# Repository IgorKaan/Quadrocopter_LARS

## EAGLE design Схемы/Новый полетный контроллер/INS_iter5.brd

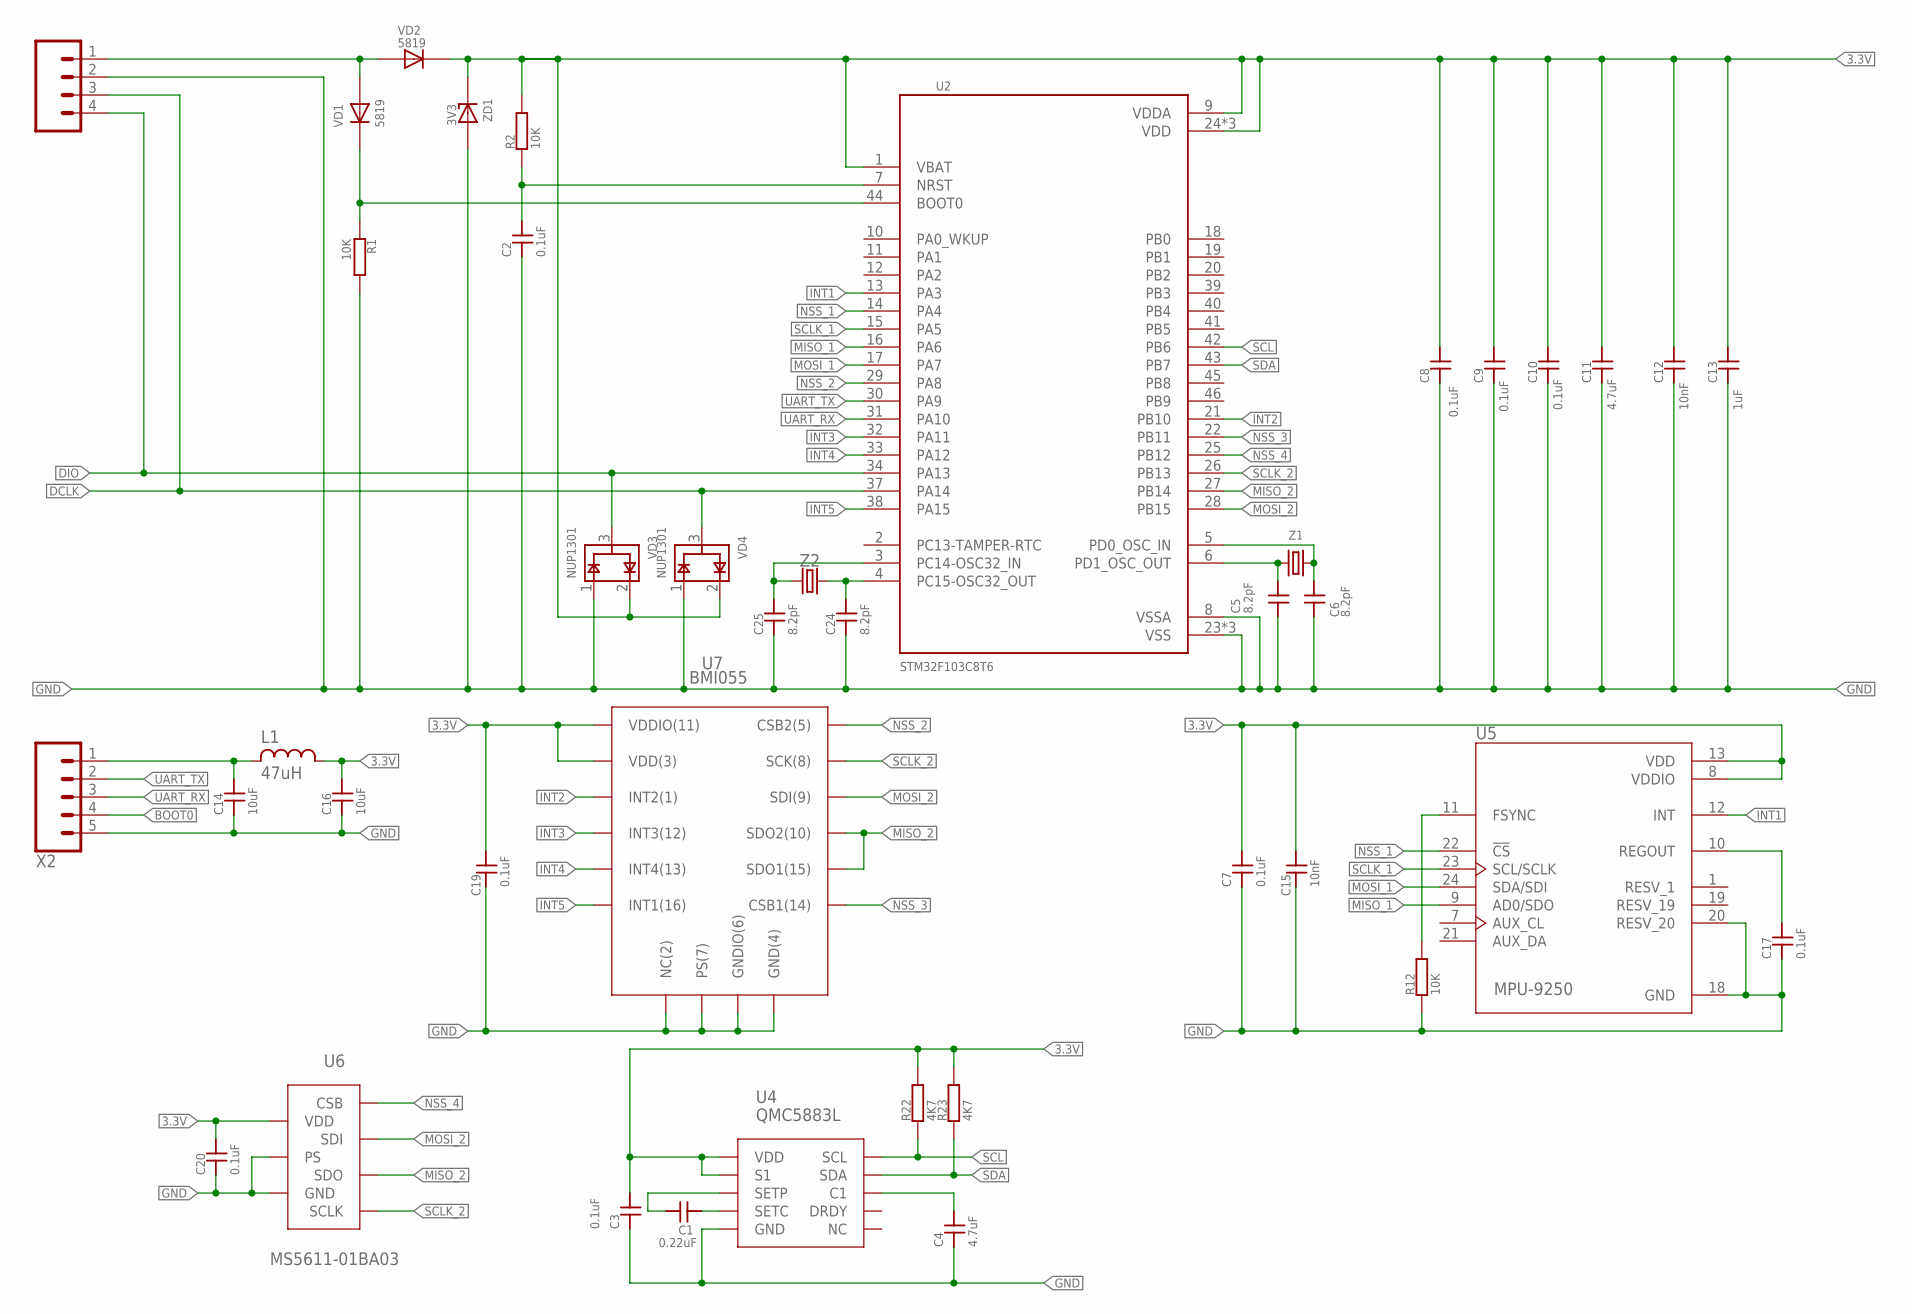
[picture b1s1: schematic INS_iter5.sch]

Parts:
C1: 0.22uF; 0402; VOLTAGE 50V
C2, C3, C7, C8, C9, C10, C17, C19, C20: 0.1uF; 0402; VOLTAGE 50V
C4, C11: 4.7uF; 0402; VOLTAGE 50V
C5, C6, C24, C25: 8.2pF; 0402; VOLTAGE 50V
C12, C15: 10nF; 0402; VOLTAGE 50V
C13: 1uF; 0402; VOLTAGE 50V
C14, C16: 10uF; 0402; VOLTAGE 6.3V
L1: 47uH; 0603_SMALL
R1, R2, R12: 10K; 0402
R22, R23: 4K7; 0402
U2: STM32F103C8T6; QFP50P900X900X160-48N
U4: QMC5883L; QFN16(3X3)NOPAD
U5: MPU-9250; QFN40P300X300X105-24N
U6: MS5611-01BA03; QFN5X3
U7: BMI055; LGA16PIN
VD1, VD2: 5819; 0402
VD3, VD4: NUP1301; SOT23
X1: 1X4DUPON; 1X04DUPON_2MM
X2: 1X5FFC5-1MM; FFC-1MM_5
Z1: 8MHz; CRYSTAL-SMD-3.2X2.5MM
Z2: CRYSTAL2FOOT; CRYSTAL-SMD-3.2X1.5X90MM
ZD1: 3V3; SOD-323

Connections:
3.3V: C3.2, C7.2, C8.2, C9.2, C10.2, C11.2, C12.2, C13.2, C15.2, C16.2, C19.2, C20.2, L1.P$2 (2), R2.2, R22.2, R23.2, U2.1 (VBAT), U2.9 (VDDA), U2.24 (VDD), U2.36 (VDD), U2.48 (VDD), U4.2 (VDD), U4.4 (S1), U4.13 (VDD), U5.8 (VDDIO), U5.13 (VDD), U6.P$4 (VDD), U7.P$3 (VDD(3)), U7.P$11 (VDDIO(11)), VD2.1 (C), VD3.2 (VCC), VD4.2 (VCC), ZD1.2 (C)
3.3V_S: VD1.2 (A), VD2.2 (A), X1.1
BOOT0: R1.1, U2.44 (BOOT0), VD1.1 (C), X2.4
DCLK: U2.37 (PA14), VD4.3 (I/O), X1.3
DIO: U2.34 (PA13), VD3.3 (I/O), X1.4
GND: C2.1, C3.1, C4.1, C5.1, C6.1, C7.1, C8.1, C9.1, C10.1, C11.1, C12.1, C13.1, C14.1, C15.1, C16.1, C17.1, C19.1, C20.1, C24.1, C25.1, R1.2, R12.1, U2.8 (VSSA), U2.23 (VSS), U2.35 (VSS), U2.47 (VSS), U4.9 (GND), U4.11 (GND), U5.18 (GND), U5.20 (RESV_20), U6.P$2 (GND), U6.P$3 (PS), U7.P$2 (NC(2)), U7.P$4 (GND(4)), U7.P$6 (GNDIO(6)), U7.P$7 (PS(7)), VD3.1 (GND), VD4.1 (GND), X1.2, X2.5, ZD1.1 (A)
INT1: U2.13 (PA3), U5.12 (INT)
INT2: U2.21 (PB10), U7.P$1 (INT2(1))
INT3: U2.32 (PA11), U7.P$12 (INT3(12))
INT4: U2.33 (PA12), U7.P$13 (INT4(13))
INT5: U2.38 (PA15), U7.P$16 (INT1(16))
MISO_1: U2.16 (PA6), U5.9 (AD0/SDO)
MISO_2: U2.27 (PB14), U6.P$7 (SDO), U7.P$10 (SDO2(10)), U7.P$15 (SDO1(15))
MOSI_1: U2.17 (PA7), U5.24 (SDA/SDI)
MOSI_2: U2.28 (PB15), U6.P$6 (SDI), U7.P$9 (SDI(9))
unnamed: C25.2, U2.3 (PC14-OSC32_IN), Z2.P$1 (1)
unnamed: C2.2, R2.1, U2.7 (NRST)
unnamed: C24.2, U2.4 (PC15-OSC32_OUT), Z2.P$2 (2)
unnamed: C17.2, U5.10 (REGOUT)
unnamed: R12.2, U5.11 (FSYNC)
unnamed: C14.2, L1.P$1 (1), X2.1
unnamed: C5.2, U2.6 (PD1_OSC_OUT), Z1.1
unnamed: C6.2, U2.5 (PD0_OSC_IN), Z1.3 (2)
unnamed: C1.2, U4.12 (SETC)
unnamed: C1.1, U4.8 (SETP)
unnamed: C4.2, U4.10 (C1)
NSS_1: U2.14 (PA4), U5.22 (!CS)
NSS_2: U2.29 (PA8), U7.P$5 (CSB2(5))
NSS_3: U2.22 (PB11), U7.P$14 (CSB1(14))
NSS_4: U2.25 (PB12), U6.P$1 (CSB), U6.P$8 (CSB)
SCL: R22.1, U2.42 (PB6), U4.1 (SCL)
SCLK_1: U2.15 (PA5), U5.23 (SCL/SCLK)
SCLK_2: U2.26 (PB13), U6.P$5 (SCLK), U7.P$8 (SCK(8))
SDA: R23.1, U2.43 (PB7), U4.16 (SDA)
UART_RX: U2.31 (PA10), X2.3
UART_TX: U2.30 (PA9), X2.2

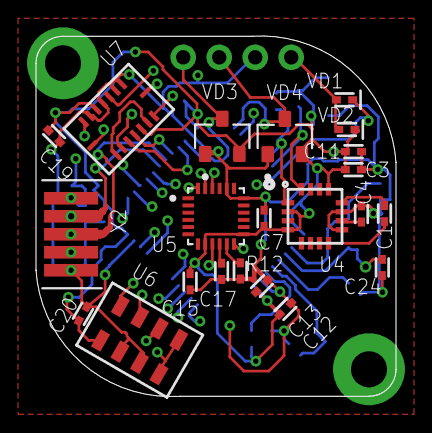
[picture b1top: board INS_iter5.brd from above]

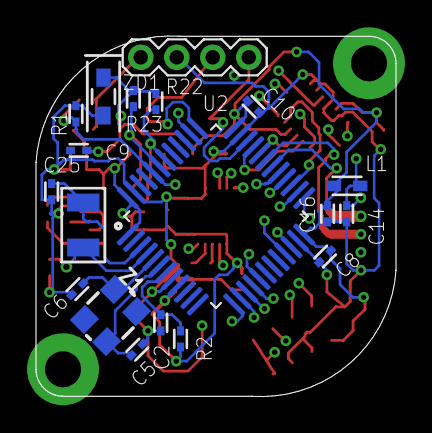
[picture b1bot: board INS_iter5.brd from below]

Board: 4 copper layers, 20.0 x 20.0 mm, 41 parts (19 on the bottom side), 36 nets.

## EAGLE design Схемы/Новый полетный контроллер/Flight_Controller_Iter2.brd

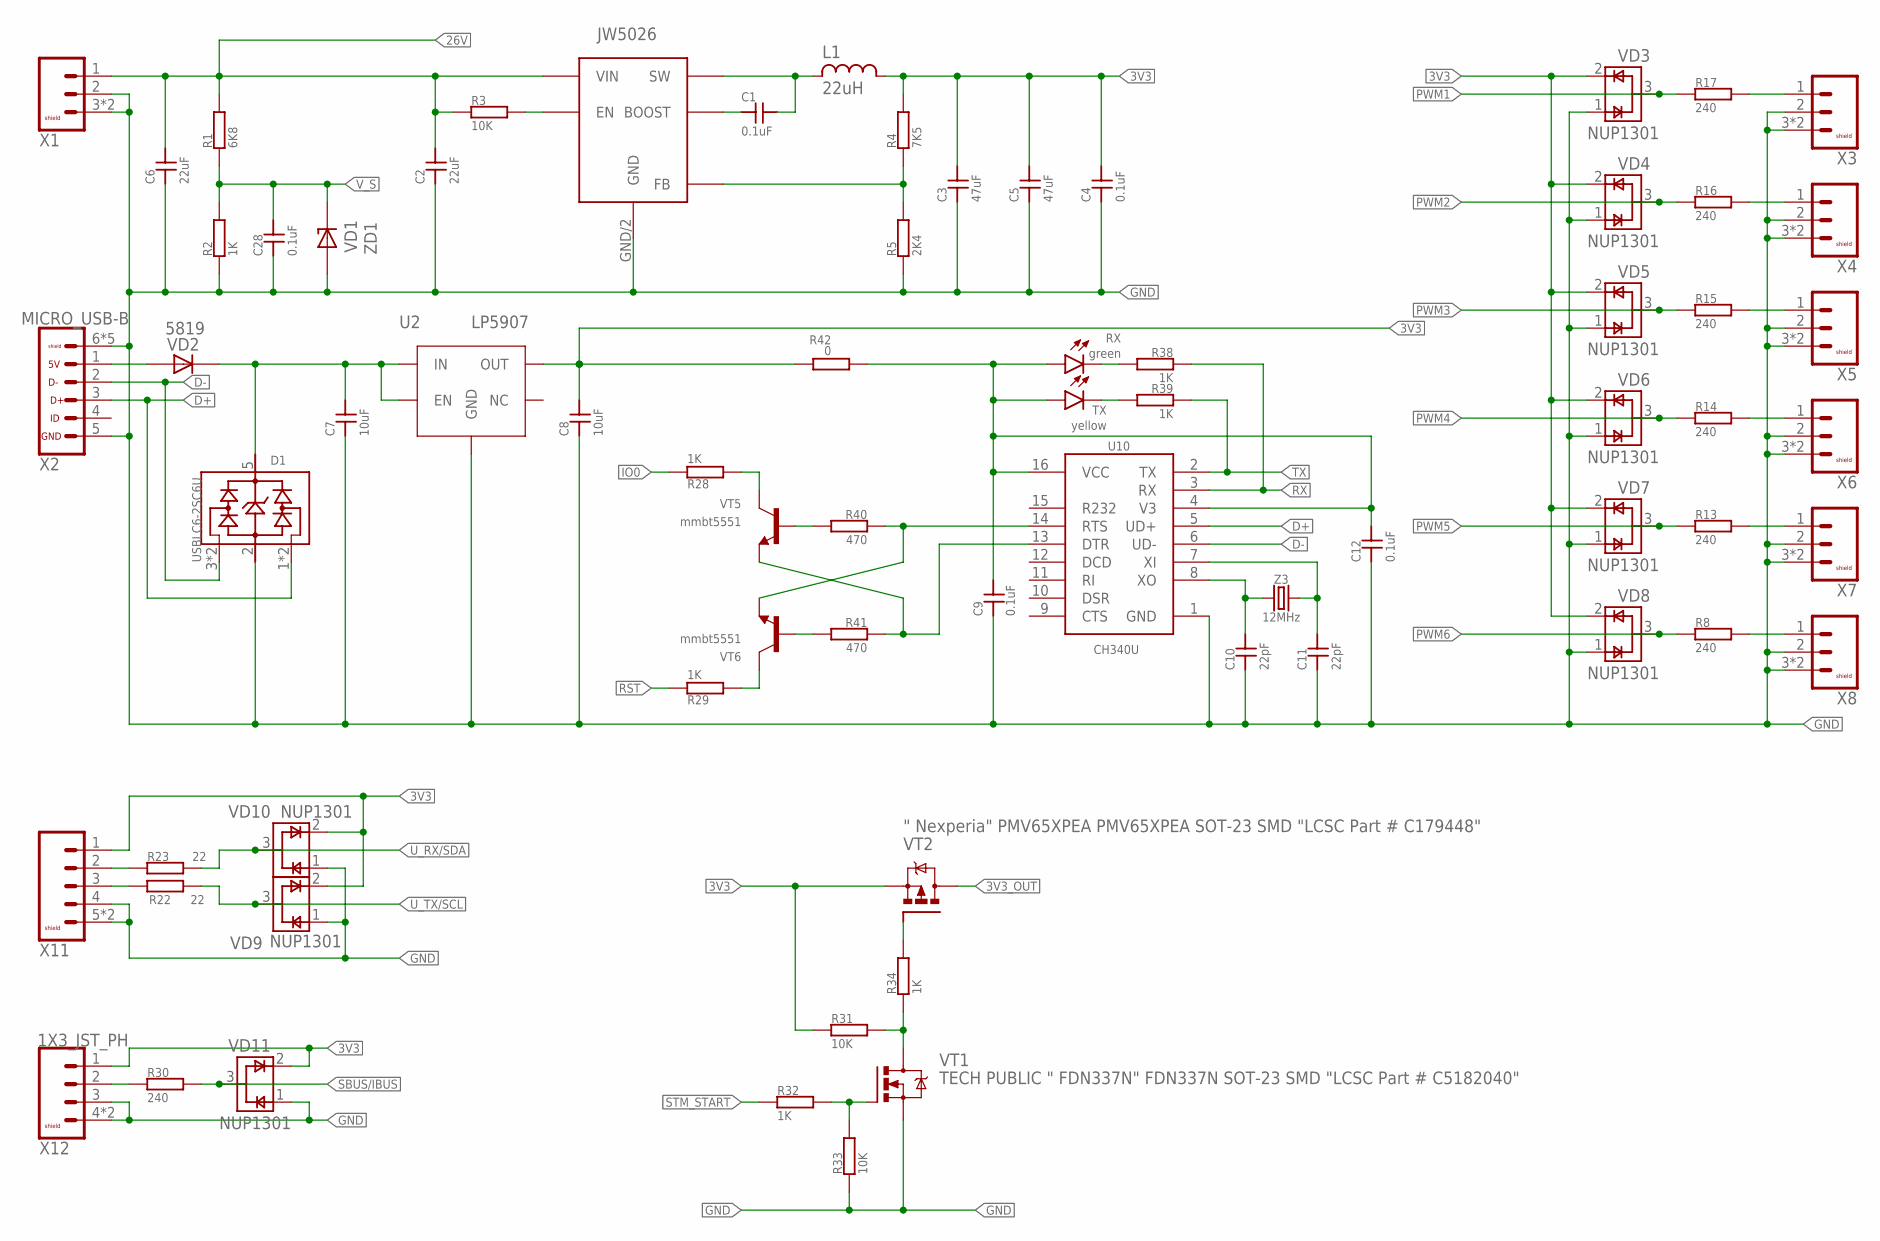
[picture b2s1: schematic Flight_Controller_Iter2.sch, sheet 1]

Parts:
C1, C9, C12, C28: 0.1uF; 0402; VOLTAGE 16V
C2, C6: 22uF; 0805; VOLTAGE 35V
C3, C5: 47uF; 0603_SMALL; VOLTAGE 6.3V
C4: 0.1uF; 0603_SMALL; VOLTAGE 50V
C7, C8: 10uF; 0402; VOLTAGE 16V
C10, C11: 22pF; 0402; VOLTAGE 16V
D1: USBLC6-2SC6U; SOT23-6
L1: 22uH; 0420CDMC
R1: 6K8; 0402
R2, R28, R29, R32, R34, R38, R39: 1K; 0402
R3, R31, R33: 10K; 0402
R4: 7K5; 0402
R5: 2K4; 0402
R8, R13, R14, R15, R16, R17, R30: 240; 0402
R22, R23: 22; 0402
R40, R41: 470; 0402
R42: 0; 0402
RX: green; 0603
TX: yellow; 0603
U1: JW5026; SOT-23-6
U2: LP5907; SOT-23-5
U10: CH340U; SOIC-16
VD1: ZD1; SOD-323
VD2: 5819; SOD-323
VD3, VD4, VD5, VD6, VD7, VD8, VD9, VD10, VD11: NUP1301; SOT23
VT1: TECH PUBLIC " FDN337N" FDN337N SOT-23 SMD "LCSC P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; SOT-23
VT2: " Nexperia" PMV65XPEA PMV65XPEA SOT-23 SMD "LCSC 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; SOT-23
VT5, VT6: mmbt5551; SOT-23
X1, X3, X4, X5, X6, X7, X8: 1X2_JST_PH_LF2; JST-PH-SM2-(LF)
X2: MICRO_USB-B; 1981584-1
X11: 1X4_JST_PH_2JST_PH_SM4_2MM(LF); JST-PH-SM4-(LF)
X12: 1X3_JST_PH; JST-PH-SM3-(LF)
Z3: 12MHz; CRYSTAL-SMD-3.2X2.5MM

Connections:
3V3: C3.P$2, C4.P$2, C5.P$2, C8.2, L1.2, R4.2, R31.1, R42.2, U2.5 (OUT), VD3.2 (VCC), VD4.2 (VCC), VD5.2 (VCC), VD6.2 (VCC), VD7.2 (VCC), VD8.2 (VCC), VD9.2 (VCC), VD10.2 (VCC), VD11.2 (VCC), VT2.2 (S), X11.1, X12.1; also elsewhere on the board
3V3_OUT: VT2.3 (D); also elsewhere on the board
26V: C2.P$2, C6.P$2, R1.2, R3.1, U1.IN/5 (VIN), X1.1
D+: D1.1 (I/O1), D1.6 (I/O1), U10.5 (UD+), X2.3 (D+)
D-: D1.3 (I/O2), D1.4 (I/O2), U10.6 (UD-), X2.2 (D-)
DTR: R41.1, U10.13 (DTR), VT5.2 (E)
GND: C2.P$1, C3.P$1, C4.P$1, C5.P$1, C6.P$1, C7.1, C8.1, C9.1, C10.1, C11.1, C12.1, C28.1, D1.2 (GND), R2.1, R5.1, R33.1, U1.GND/2 (GND), U2.2 (GND), U10.1 (GND), VD1.1 (A), VD3.1 (GND), VD4.1 (GND), VD5.1 (GND), VD6.1 (GND), VD7.1 (GND), VD8.1 (GND), VD9.1 (GND), VD10.1 (GND), VD11.1 (GND), VT1.2 (S), X1.2, X1.3, X1.4 (3), X2.5 (GND), X2.6 (SHIELD), X2.P$1 (SHIELD), X2.P$2 (SHIELD), X2.P$3 (SHIELD), X2.P$7 (SHIELD), X3.2, X3.3, X3.4 (3), X4.2, X4.3, X4.4 (3), X5.2, X5.3, X5.4 (3), X6.2, X6.3, X6.4 (3), X7.2, X7.3, X7.4 (3), X8.2, X8.3, X8.4 (3), X11.4, X11.5, X11.6 (5), X12.3, X12.4, X12.5 (4); also elsewhere on the board
IO0: R28.1; also elsewhere on the board
unnamed: VD2.1 (A), X2.1 (5V)
unnamed: C7.2, D1.5 (VBUS), U2.1 (IN), U2.3 (EN), VD2.2 (C)
unnamed: R3.2, U1.EN/4 (EN)
unnamed: C1.1, U1.BOOST/1 (BOOST)
unnamed: C1.2, L1.1, U1.SW/6 (SW)
unnamed: R4.1, R5.2, U1.FB/3 (FB)
unnamed: R17.2, X3.1
unnamed: R16.2, X4.1
unnamed: R15.2, X5.1
unnamed: R14.2, X6.1
unnamed: R13.2, X7.1
unnamed: R8.2, X8.1
unnamed: R38.2, RX.P$1 (C)
unnamed: R39.2, TX.P$1 (C)
unnamed: R28.2, VT5.3 (C)
unnamed: C10.2, U10.8 (XO), Z3.3 (2)
unnamed: C11.2, U10.7 (XI), Z3.1
unnamed: R40.2, VT5.1 (B)
unnamed: R41.2, VT6.1 (B)
unnamed: R29.2, VT6.3 (C)
unnamed: R23.1, X11.2
unnamed: R22.1, X11.3
unnamed: R30.1, X12.2
unnamed: R31.2, R34.1, VT1.3 (D)
unnamed: R32.2, R33.2, VT1.1 (G)
unnamed: R34.2, VT2.1 (G)
PWM1: R17.1, VD3.3 (I/O); also elsewhere on the board
PWM2: R16.1, VD4.3 (I/O); also elsewhere on the board
PWM3: R15.1, VD5.3 (I/O); also elsewhere on the board
PWM4: R14.1, VD6.3 (I/O); also elsewhere on the board
PWM5: R13.1, VD7.3 (I/O); also elsewhere on the board
PWM6: R8.1, VD8.3 (I/O); also elsewhere on the board
RST: R29.1; also elsewhere on the board
RTS: R40.1, U10.14 (RTS), VT6.2 (E)
RX: R38.1, U10.3 (RX); also elsewhere on the board
SBUS/IBUS: R30.2, VD11.3 (I/O); also elsewhere on the board
STM_START: R32.1; also elsewhere on the board
TX: R39.1, U10.2 (TX); also elsewhere on the board
U_RX/SDA: R23.2, VD10.3 (I/O); also elsewhere on the board
U_TX/SCL: R22.2, VD9.3 (I/O); also elsewhere on the board
VCC_1: C9.2, C12.2, R42.1, RX.P$2 (A), TX.P$2 (A), U10.4 (V3), U10.16 (VCC)
V_S: C28.2, R1.1, R2.2, VD1.2 (C); also elsewhere on the board

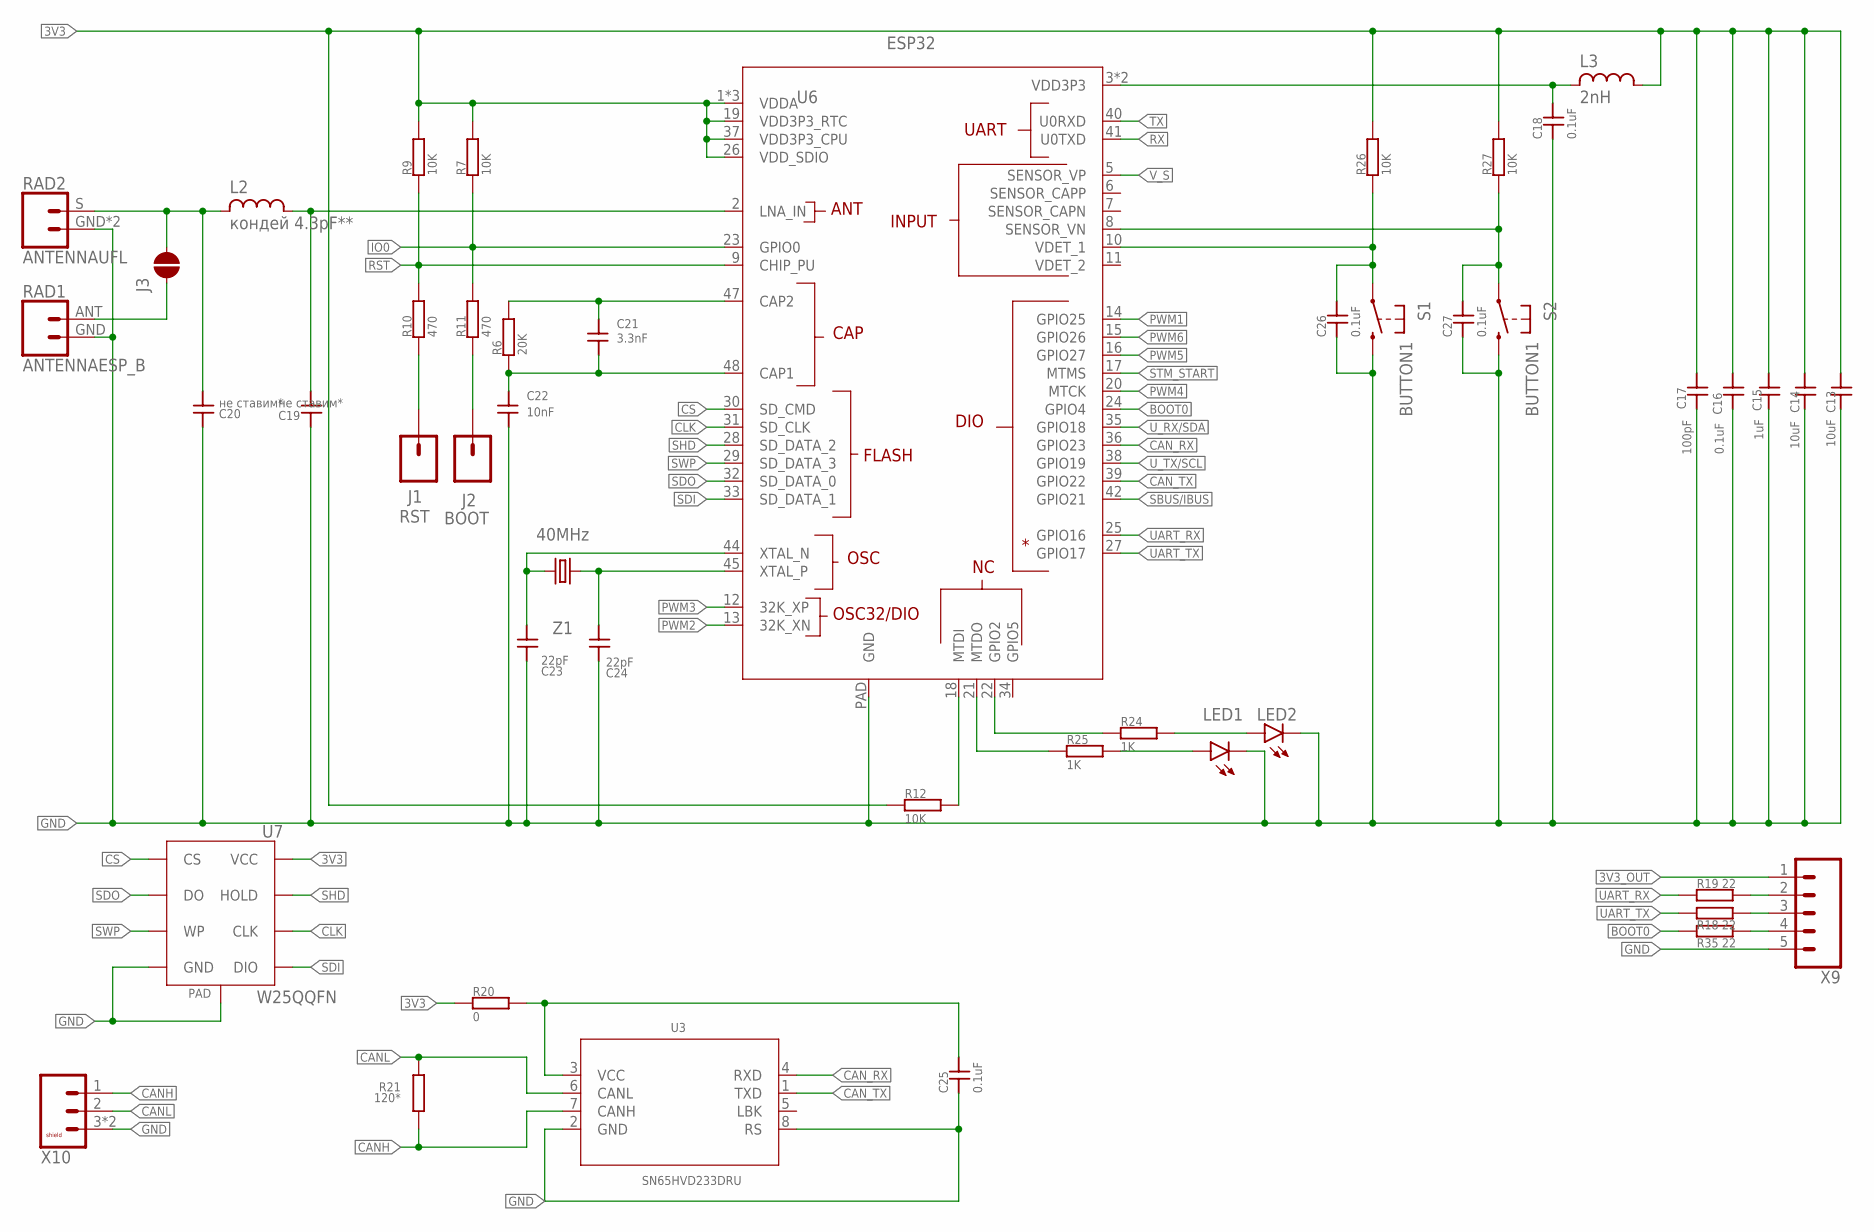
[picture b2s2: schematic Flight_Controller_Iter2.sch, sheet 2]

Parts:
C13, C14: 10uF; 0402; VOLTAGE 16V
C15: 1uF; 0402; VOLTAGE 16V
C16, C18, C25, C26, C27: 0.1uF; 0402; VOLTAGE 16V
C17: 100pF; 0402; VOLTAGE 16V
C19, C20: не ставим*; 0402
C21: 3.3nF; 0402; VOLTAGE 16V
C22: 10nF; 0402; VOLTAGE 16V
C23, C24: 22pF; 0402; VOLTAGE 16V
J1: RST; 1X1_PAD_T
J2: BOOT; 1X1_PAD_T
J3: TEST_PAD1X1MM; TEST_PAD
L2: кондей 4.3pF**; 0402
L3: 2nH; 0402
LED1, LED2: LED0402; 0402
R6: 20K; 0402
R7, R9, R12, R26, R27: 10K; 0402
R10, R11: 470; 0402
R18, R19, R35: 22; 0402
R20: 0; 0402
R21: 120*; 0603_SMALL
R24, R25: 1K; 0402
RAD1: ANTENNAESP_B; 2.4GHZB
RAD2: ANTENNAUFL; U.FL
S1, S2: BUTTON1; 3X4X2
U3: SN65HVD233DRU; SOIC-8
U6: ESP32; QFN48(5X5MM)
U7: W25QQFN; WSON8X6-MM
X9: 1X5FFC5-1MM; FFC-1MM_5
X10: 1X2_JST_PH_LF2; JST-PH-SM2-(LF)
Z1: 40MHz; CRYSTAL-SMD-3.2X2.5MM

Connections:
3V3: C13.2, C14.2, C15.2, C16.2, C17.2, L3.2, R7.2, R9.2, R12.1, R20.1, R26.2, R27.2, U6.1 (VDDA), U6.19 (VDD3P3_RTC), U6.26 (VDD_SDIO), U6.37 (VDD3P3_CPU), U6.43 (VDDA), U6.46 (VDDA), U7.P$9 (VCC); also elsewhere on the board
3V3_OUT: X9.1; also elsewhere on the board
BOOT0: R35.1, U6.24 (GPIO4)
CANH: R21.P$1, U3.7 (CANH), X10.1
CANL: R21.P$2, U3.6 (CANL), X10.2
CAN_RX: U3.4 (RXD), U6.36 (GPIO23)
CAN_TX: U3.1 (TXD), U6.39 (GPIO22)
CLK: U6.31 (SD_CLK), U7.P$7 (CLK)
CS: U6.30 (SD_CMD), U7.P$2 (CS)
GND: C13.1, C14.1, C15.1, C16.1, C17.1, C18.1, C19.1, C20.1, C22.1, C23.1, C24.1, C25.1, C26.1, C27.1, LED1.1 (C), LED2.1 (C), RAD1.GND, RAD2.GND, RAD2.GND1 (GND), S1.P$2 (4), S2.P$2 (4), U3.2 (GND), U3.8 (RS), U6.PAD (GND), U7.P$1, U7.P$5 (GND), X9.5, X10.3, X10.4 (3); also elsewhere on the board
IO0: R7.1, R11.2, U6.23 (GPIO0); also elsewhere on the board
LED1: R24.1, U6.22 (GPIO2)
LED2: R25.1, U6.21 (MTDO)
unnamed: R18.2, X9.3
unnamed: C19.2, L2.2, U6.2 (LNA_IN)
unnamed: C20.2, J3.P$2, L2.1, RAD2.S (ANTENNA)
unnamed: C21.2, R6.2, U6.47 (CAP2)
unnamed: C21.1, C22.2, R6.1, U6.48 (CAP1)
unnamed: C23.2, U6.44 (XTAL_N), Z1.3 (2)
unnamed: C24.2, U6.45 (XTAL_P), Z1.1
unnamed: R12.2, U6.18 (MTDI)
unnamed: C18.2, L3.1, U6.3 (VDD3P3), U6.4 (VDD3P3)
unnamed: R19.2, X9.2
unnamed: LED2.2 (A), R24.2
unnamed: LED1.2 (A), R25.2
unnamed: J1.P$1, R10.1
unnamed: J2.P$1, R11.1
unnamed: J3.P$1, RAD1.ANT (ANTENNA)
unnamed: R35.2, X9.4
PWM1: U6.14 (GPIO25); also elsewhere on the board
PWM2: U6.13 (32K_XN); also elsewhere on the board
PWM3: U6.12 (32K_XP); also elsewhere on the board
PWM4: U6.20 (MTCK); also elsewhere on the board
PWM5: U6.16 (GPIO27); also elsewhere on the board
PWM6: U6.15 (GPIO26); also elsewhere on the board
RST: R9.1, R10.2, U6.9 (CHIP_PU); also elsewhere on the board
RX: U6.41 (U0TXD); also elsewhere on the board
SBUS/IBUS: U6.42 (GPIO21); also elsewhere on the board
SDI: U6.33 (SD_DATA_1), U7.P$6 (DIO)
SDO: U6.32 (SD_DATA_0), U7.P$3 (DO)
SHD: U6.28 (SD_DATA_2), U7.P$8 (HOLD)
STM_START: U6.17 (MTMS); also elsewhere on the board
SW1: C27.2, R27.1, S2.P$1 (3), U6.8 (SENSOR_VN)
SW2: C26.2, R26.1, S1.P$1 (3), U6.10 (VDET_1)
SWP: U6.29 (SD_DATA_3), U7.P$4 (WP)
TX: U6.40 (U0RXD); also elsewhere on the board
UART_RX: R19.1, U6.25 (GPIO16)
UART_TX: R18.1, U6.27 (GPIO17)
U_RX/SDA: U6.35 (GPIO18); also elsewhere on the board
U_TX/SCL: U6.38 (GPIO19); also elsewhere on the board
VCC: C25.2, R20.2, U3.3 (VCC)
V_S: U6.5 (SENSOR_VP); also elsewhere on the board

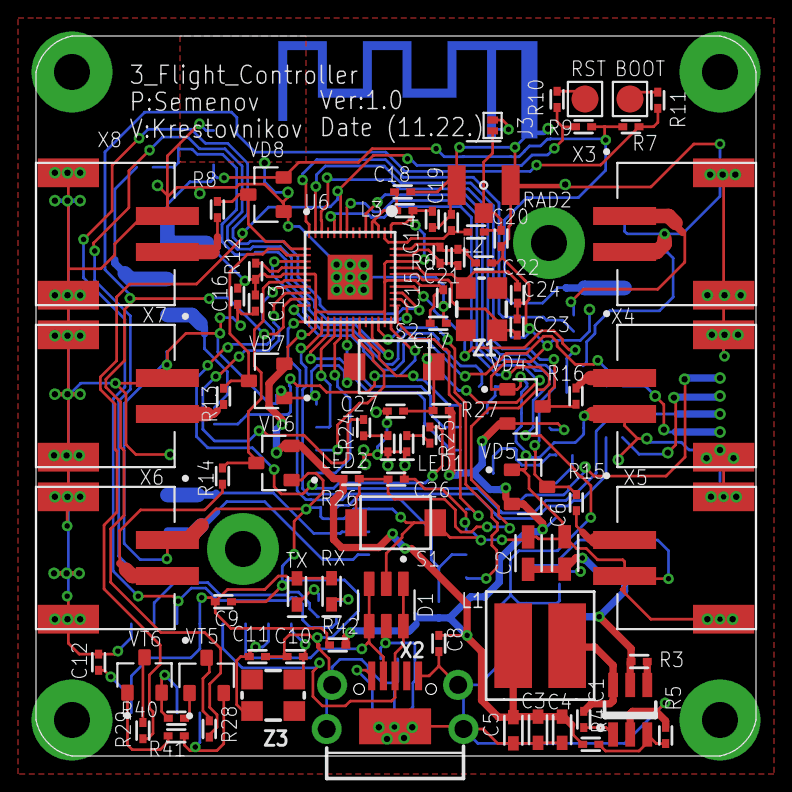
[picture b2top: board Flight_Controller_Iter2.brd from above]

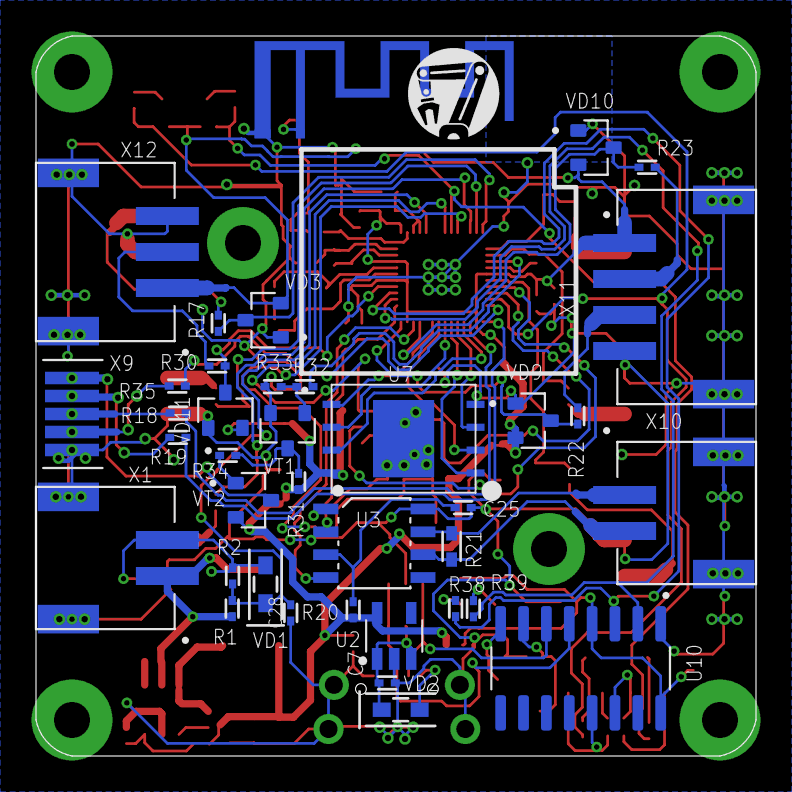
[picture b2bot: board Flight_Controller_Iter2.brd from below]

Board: 2 copper layers, 40.0 x 40.0 mm, 118 parts (37 on the bottom side), 84 nets.

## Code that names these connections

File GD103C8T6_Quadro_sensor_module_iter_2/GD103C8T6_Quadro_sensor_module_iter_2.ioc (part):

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Mcu.Name=STM32F103C(8-B)Tx
Mcu.Package=LQFP48
Mcu.UserName=STM32F103C8Tx
PA10.Mode=Asynchronous
PA10.Signal=USART1_RX
PA11.GPIOParameters=GPIO_Label
PA11.GPIO_Label=INT_3
PA11.Signal=GPXTI11
PA12.GPIOParameters=GPIO_Label
PA12.GPIO_Label=INT_4
PA12.Signal=GPXTI12
PA13.Mode=Serial_Wire
PA13.Signal=SYS_JTMS-SWDIO
PA14.Mode=Serial_Wire
PA14.Signal=SYS_JTCK-SWCLK
PA15.GPIOParameters=GPIO_Label
PA15.GPIO_Label=INT_5
PA15.Signal=GPXTI15
PA3.GPIOParameters=GPIO_Label
PA3.GPIO_Label=INT_MPU
PA3.Signal=GPXTI3
PA4.GPIOParameters=GPIO_Label
PA4.GPIO_Label=NSS_MPU
PA4.Signal=GPIO_Output
PA5.Mode=Full_Duplex_Master
PA5.Signal=SPI1_SCK
PA6.Mode=Full_Duplex_Master
PA6.Signal=SPI1_MISO
PA7.Mode=Full_Duplex_Master
PA7.Signal=SPI1_MOSI
PA8.GPIOParameters=GPIO_Label
PA8.GPIO_Label=NSS_2
PA8.Signal=GPIO_Output
PA9.Mode=Asynchronous
PA9.Signal=USART1_TX
PB10.GPIOParameters=GPIO_Label
PB10.GPIO_Label=INT_2
PB10.Signal=GPXTI10
PB11.GPIOParameters=GPIO_Label
PB11.GPIO_Label=NSS_3
PB11.Signal=GPIO_Output
PB12.GPIOParameters=GPIO_Label
PB12.GPIO_Label=NSS_MS
PB12.Signal=GPIO_Output
PB13.Mode=Full_Duplex_Master
PB13.Signal=SPI2_SCK
PB14.Mode=Full_Duplex_Master
PB14.Signal=SPI2_MISO
PB15.Mode=Full_Duplex_Master
PB15.Signal=SPI2_MOSI
PB6.Mode=I2C
PB6.Signal=I2C1_SCL
PB7.Mode=I2C
PB7.Signal=I2C1_SDA
PD0-OSC_IN.Mode=HSE-External-Oscillator
PD0-OSC_IN.Signal=RCC_OSC_IN
PD1-OSC_OUT.Mode=HSE-External-Oscillator
PD1-OSC_OUT.Signal=RCC_OSC_OUT
RCC.SYSCLKFreq_VALUE=72000000
RCC.SYSCLKSource=RCC_SYSCLKSOURCE_PLLCLK
board=custom

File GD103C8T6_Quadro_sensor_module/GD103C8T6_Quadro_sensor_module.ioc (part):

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Mcu.Name=STM32F103C(8-B)Tx
Mcu.Package=LQFP48
Mcu.UserName=STM32F103C8Tx
PA11.Mode=CAN_Activate
PA11.Signal=CAN_RX
PA12.Mode=CAN_Activate
PA12.Signal=CAN_TX
PA13.Mode=Serial_Wire
PA13.Signal=SYS_JTMS-SWDIO
PA14.Mode=Serial_Wire
PA14.Signal=SYS_JTCK-SWCLK
PA15.GPIOParameters=GPIO_Label
PA15.GPIO_Label=LED1
PA15.Signal=GPIO_Output
PA2.Mode=Asynchronous
PA2.Signal=USART2_TX
PA3.Mode=Asynchronous
PA3.Signal=USART2_RX
PA4.GPIOParameters=GPIO_Label
PA4.GPIO_Label=NSS_MPU
PA4.Signal=GPIO_Output
PA5.Mode=Full_Duplex_Master
PA5.Signal=SPI1_SCK
PA6.Mode=Full_Duplex_Master
PA6.Signal=SPI1_MISO
PA7.Mode=Full_Duplex_Master
PA7.Signal=SPI1_MOSI
PA8.GPIOParameters=GPIO_Label
PA8.GPIO_Label=NSS_W25Q
PA8.Signal=GPIO_Output
PA9.GPIOParameters=GPIO_Label
PA9.GPIO_Label=NSS_MS
PA9.Signal=GPIO_Output
PB13.Mode=Full_Duplex_Master
PB13.Signal=SPI2_SCK
PB14.Mode=Full_Duplex_Master
PB14.Signal=SPI2_MISO
PB15.Mode=Full_Duplex_Master
PB15.Signal=SPI2_MOSI
PB3.GPIOParameters=GPIO_Label
PB3.GPIO_Label=LED2
PB3.Signal=GPIO_Output
PB4.GPIOParameters=GPIO_Label
PB4.GPIO_Label=LED3
PB4.Signal=GPIO_Output
PD0-OSC_IN.Mode=HSE-External-Oscillator
PD0-OSC_IN.Signal=RCC_OSC_IN
PD1-OSC_OUT.Mode=HSE-External-Oscillator
PD1-OSC_OUT.Signal=RCC_OSC_OUT
RCC.SYSCLKFreq_VALUE=36000000
RCC.SYSCLKSource=RCC_SYSCLKSOURCE_PLLCLK
board=custom

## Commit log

2022-11-30 init
2022-11-30 add quad_main
2022-12-05 some changes
2022-12-05 05.12
2022-12-05 work code 06.12.22
2022-12-05 work code 06.12.22 v2
2022-12-05 roll pitch send 1 can packet
2022-12-08 added filter
2022-12-08 added threads, config, PID class
2022-12-08 solves yaw compensation problem
2022-12-13 13.12.22
2022-12-15 15.12.22
2022-12-15 stab test code
2022-12-15 regulator 1000 hz & power reg changes OK
2022-12-19 added barometer
2022-12-20 add TFMini, conf changes
2022-12-29 gitignore mod
2023-01-11 yaw fix
2023-01-13 fail
2023-01-13 13.01.23
2023-01-19 19.01.23 test OK
2023-01-23 Add arm
2023-01-27 new controller
2023-02-16 added ESP32 - GD32 bridge
2023-03-01 01.03.23 pid test OK
2023-04-04 last fix
2023-04-04 danya
2023-04-04 Найдена ошибка связанная с выводом в плоттер. Скорректированы коэффициенты по Яу
2023-04-04 stable UART
2023-04-05 Примерно выбраный коэффициенты ПИД-регулятора
